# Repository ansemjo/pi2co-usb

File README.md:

# pi2co-usb

This project is based on [i2c-tiny-usb](https://github.com/harbaum/I2C-Tiny-USB/) by Till Harbaum and the [V-USB stack](https://www.obdev.at/products/vusb/index.html) by Objective Development. It uses the fact that you can implement a low-speed USB device with the IO pins on an Atmel AVR chip to create a very simple I2C bridge.

## Hardware

In the original `i2c-tiny-usb` implementation, an Atmel AVR ATtiny45 was used with an external oscillator. Unfortunately this meant, that you needed to use all six pins on the chip, reconfigure the RESET pin and therefore needed a high-voltage serial programmer (HVSP) should anything go wrong.

On more recent Digispark devices, which use an ATtiny85, a modified version of the V-USB stack is used with only the internal PLL oscillator calibrated to 16.5 MHz. No external chrystal is required, ISP remains available and you can even connect an indicator LED on the remaining pin.

I had a couple of Atmel AVR ATtiny85V-10PU chips and a small leftover piece of protoboard. Enough to build myself an I2C bridge! I used a JST-PH connector on the I2C side, which has a slightly too narrow pitch but it works out with a 4-pin connector if you solder it at the edge of the board. Also I had lots of connectors, so I could crimp myself some cables.

Here is a simple [schematic](schematic.pdf) of the protoboard version that you see below on the photos:

## Software

The firmware is almost fully plucked from Till Harbaum's `i2c-tiny-usb` project, so most credit goes to him. I converted the directory to a PlatformIO project, updated the vendored V-USB stack and modified the configuration header to use a different pinout.

It is meant to work together with a current [micronucleus](https://github.com/micronucleus/micronucleus/) bootloader, which allows loading new firmware over the same USB port that is used in the userspace firmware. This implementation also relies on the oscillator calibration included in the bootloader to achieve a stable 16.5 MHz clock.

### Flash the Bootloader

At first I used a default release for the ATtiny85 that I flashed with an ISP programmer and later changed a few options to enable the indicator LED, enter the bootloader only after shorting the RESET pin and disable the timeout. The configuration can be found in `bootloader/t85_pi2co` and can be linked or copied to a micronucleus project under `firmware/configuration/`.

For example, to compile the firmware with the config profile above and flash it with an [Adafruit FT232H breakout](https://wiki.semjonov.de/tips/arduino.html#adafruit-ftdi-ft232h-breakout-board):

```sh
make clean
make CONFIG=t85_pi2co
make CONFIG=t85_pi2co PROGRAMMER="-c ft232h" flash
make CONFIG=t85_pi2co PROGRAMMER="-c ft232h" fuse
```

After that you should be able to speak to the chip with the `micronucleus` commandline application if you connect a USB breakout appropriately. **To enter the bootloader later**, you'll need to reset the chip by briefly shorting the RESET pin to ground.

To allow normal users to speak with the bootloader, apply the
udev rules found in [49-micronucleus.rules](https://github.com/micronucleus/micronucleus/blob/e74ce6f064e0bcbe1c52459a0988187c76834222/commandline/49-micronucleus.rules).

### Flash the Firmware

Now that the bootloader works, install [PlatformIO](https://platformio.org/) and go to the `firmware/` directory. You can now compile the firmware simply by running `pio run`. PlatformIO should handle all framework and platform dependencies for you.

Afterwards flash the firmware by running:

```sh
pio run -t upload
```

**Note:** PlatformIO currently ships an outdated version of the `micronucleus` commandline tool, which won't speak to the current bootloader releases. Either update the binary in `~/.platformio/packages/tool-micronucleus/` or use a current binary with the compiled firmware directly:

```sh
micronucleus .pio/build/tiny85/firmware.hex
```

### Kernel driver

The `i2c-tiny-usb` project has been around for a while, so it already has a driver in the mainline Linux kernel. I only needed to `modprobe i2c-dev` for the device to appear. Install the `i2c-tools` in your Linux distribution of choice and start talking to I2C devices. You may need to run the tools as `root`.

As an example I am reading the date and time from a DS3231 RTC clock:

```sh
$ sudo i2cdetect -l
[sudo] password for ansemjo: 
/* ... */
i2c-10	i2c       	i2c-tiny-usb at bus 001 device 028	I2C adapter
/* ... */

$ sudo i2cdetect -y 10
     0  1  2  3  4  5  6  7  8  9  a  b  c  d  e  f
00:          -- -- -- -- -- -- -- -- -- -- -- -- -- 
10: -- -- -- -- -- -- -- -- -- -- -- -- -- -- -- -- 
20: -- -- -- -- -- -- -- -- -- -- -- -- -- -- -- -- 
30: -- -- -- -- -- -- -- -- -- -- -- -- -- -- -- -- 
40: -- -- -- -- -- -- -- -- -- -- -- -- -- -- -- -- 
50: -- -- -- -- -- -- -- 57 -- -- -- -- -- -- -- -- 
60: -- -- -- -- -- -- -- -- 68 -- -- -- -- -- -- --  << this is the rtc
70: -- -- -- -- -- -- -- --                         

$ i=0; for value in seconds minutes hours weekday day month year; do \
> printf '%7s: %s\n' $value "$(sudo i2cget -y 10 0x68 $i)"; : $((i++)); done
seconds: 0x39
minutes: 0x07
  hours: 0x19
weekday: 0x07
    day: 0x15
  month: 0x03
   year: 0x20
```

The bytes need BCD decoding but you can see the date was `2020-03-15 19:07:39`.

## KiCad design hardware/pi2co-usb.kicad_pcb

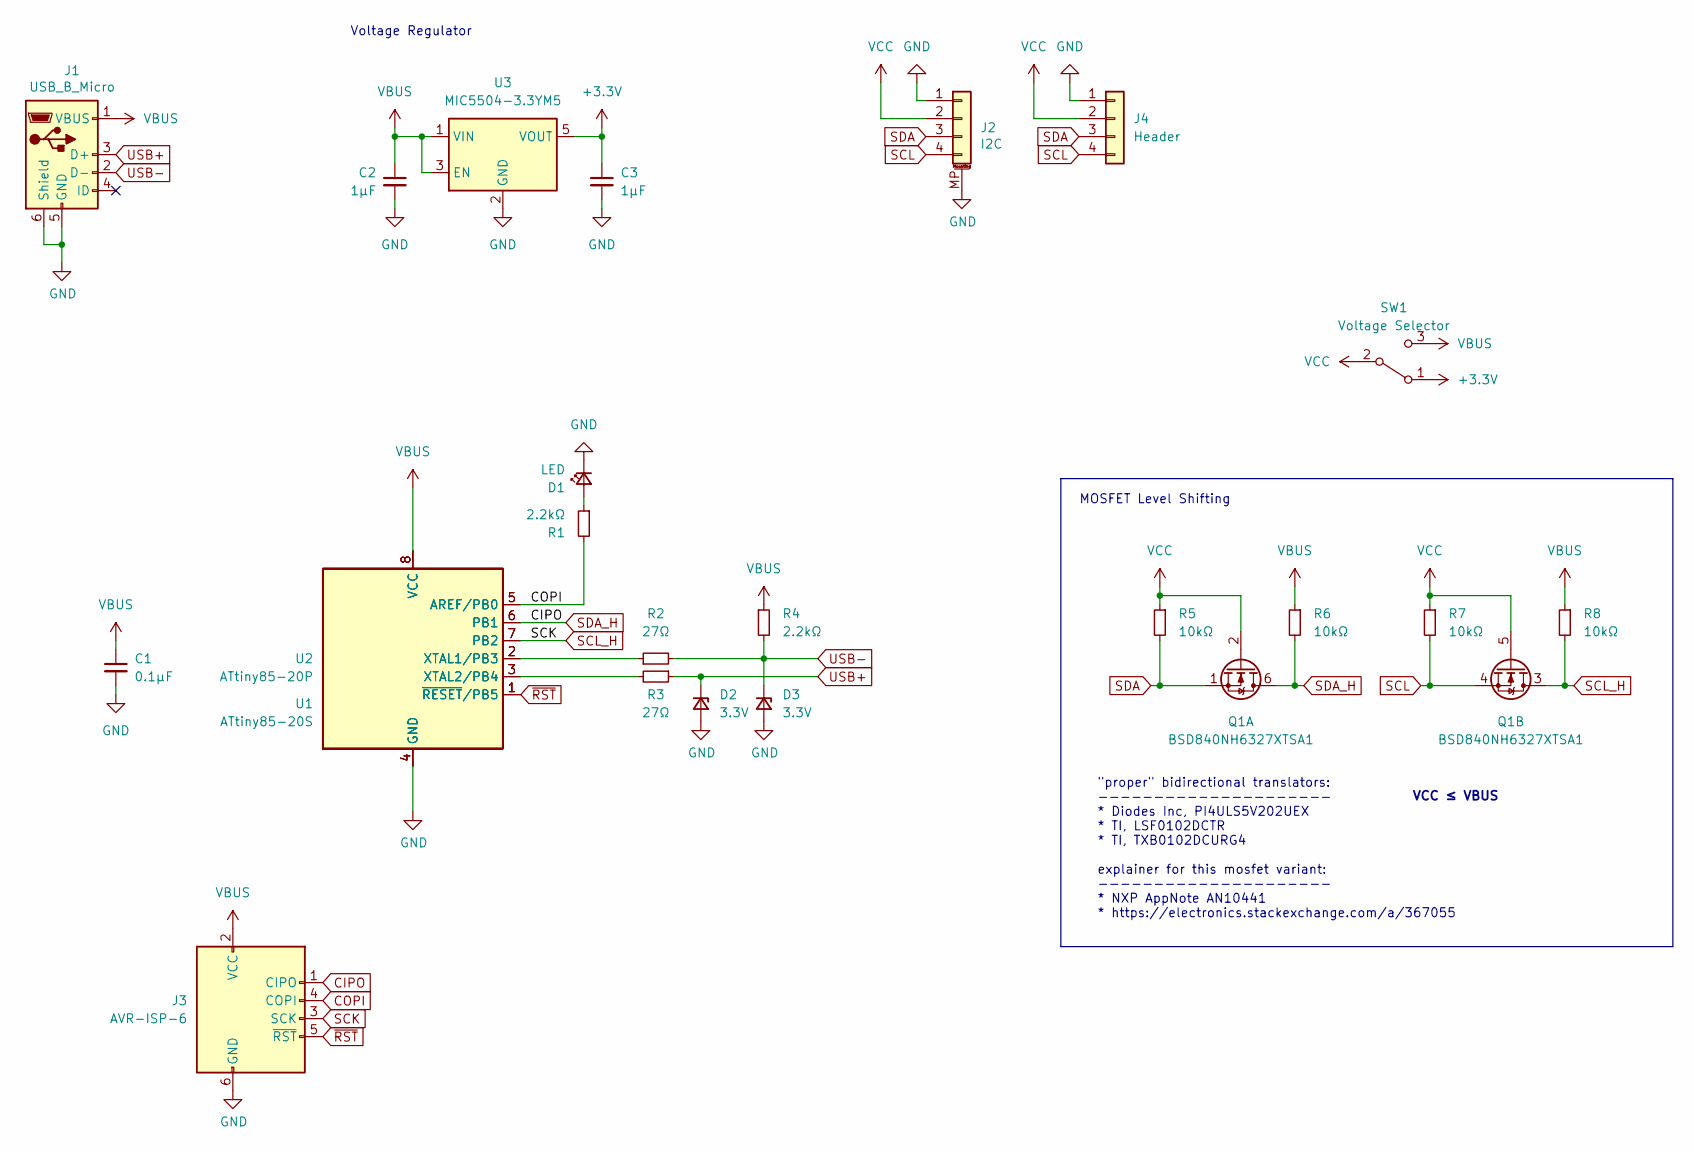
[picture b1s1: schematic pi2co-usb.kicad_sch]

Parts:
C1: 0.1µF; C_0805_2012Metric
C2, C3: 1µF; C_0805_2012Metric
D1: LED; LED_0805_2012Metric
D2, D3: 3.3V; D_SOD-123
J1: USB_B_Micro; USB_Micro-B_Amphenol_10118194_Horizontal
J2: I2C; JST_SH_SM04B-SRSS-TB_1x04-1MP_P1.00mm_Horizontal
J3: AVR-ISP-6; PinHeader_2x03_P2.54mm_Vertical
J4: Header; PinHeader_1x04_P2.54mm_Vertical
Q1: BSD840NH6327XTSA1; SOT-363_SC-70-6
R1, R4: 2.2kΩ; R_0805_2012Metric
R2, R3: 27Ω; R_0805_2012Metric
R5, R6, R7, R8: 10kΩ; R_0805_2012Metric
SW1: Voltage Selector; SW_SPDT_PCM12
U1: ATtiny85-20S; SOIC-8W_5.3x5.3mm_P1.27mm
U2: ATtiny85-20P; DIP-8_W7.62mm
U3: MIC5504-3.3YM5; SOT-23-5

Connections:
+3V3: C3.1, SW1.1 (A), U3.5 (VOUT)
CIPO: J3.1 (CIPO), Q1.6 (D), R6.2, U1.6 (PB1), U2.6 (PB1)
COPI: J3.4 (COPI), R1.2, U1.5 (AREF/PB0), U2.5 (AREF/PB0)
GND: C1.2, C2.2, C3.2, D1.1 (K), D2.2 (A), D3.2 (A), J1.5 (GND), J1.6 (Shield), J2.1, J2.MP (MountPin), J3.6 (GND), J4.1, U1.4 (GND), U2.4 (GND), U3.2 (GND)
unnamed: D1.2 (A), R1.1
unnamed: R2.1, U1.2 (XTAL1/PB3), U2.2 (XTAL1/PB3)
unnamed: R3.2, U1.3 (XTAL2/PB4), U2.3 (XTAL2/PB4)
SCK: J3.3 (SCK), Q1.3 (D), R8.2, U1.7 (PB2), U2.7 (PB2)
SCL: J2.4, J4.4, Q1.4 (S), R7.2
SDA: J2.3, J4.3, Q1.1 (S), R5.2
USB+: D2.1 (K), J1.3 (D+), R3.1
USB-: D3.1 (K), J1.2 (D-), R2.2, R4.2
VBUS: C1.1, C2.1, J1.1 (VBUS), J3.2 (VCC), R4.1, R6.1, R8.1, SW1.3 (C), U1.8 (VCC), U2.8 (VCC), U3.1 (VIN), U3.3 (EN)
VCC: J2.2, J4.2, Q1.2 (G), Q1.5 (G), R5.1, R7.1, SW1.2 (B)
~RST: J3.5 (~RST), U1.1 (~RESET/PB5), U2.1 (~RESET/PB5)

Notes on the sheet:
Voltage Regulator
MOSFET Level Shifting
VCC ≤ VBUS
"proper" bidirectional translators: --------------------- * Diodes Inc, PI4ULS5V202UEX * TI, LSF0102DCTR * TI, TXB0102DCURG4 explainer for this mosfet variant: --------------------- * NXP AppNote AN10441 * https://electronics.stackexchange.com/a/367055

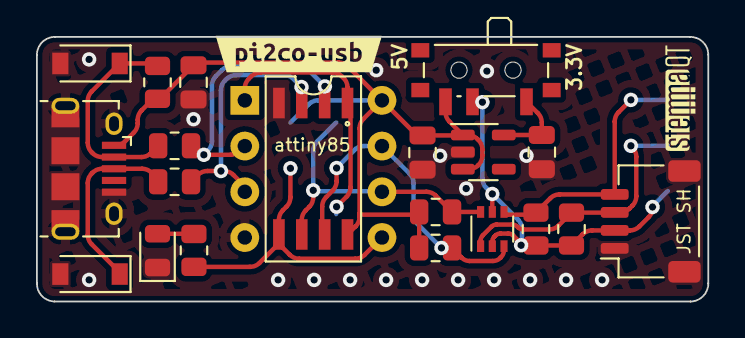
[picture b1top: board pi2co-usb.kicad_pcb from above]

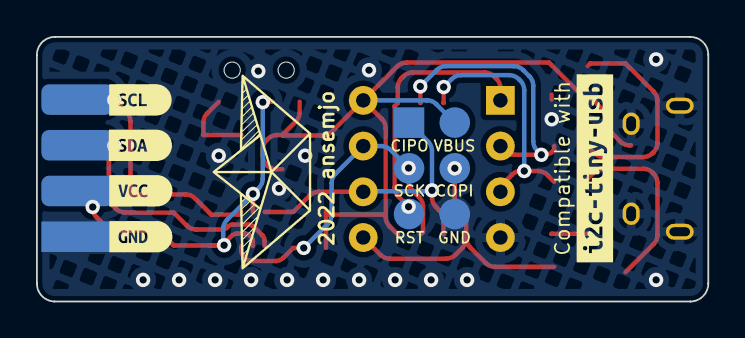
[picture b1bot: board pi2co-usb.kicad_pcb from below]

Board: 2 copper layers, 37.3 x 14.7 mm, 29 parts (7 on the bottom side), 15 nets.

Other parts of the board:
kibuzzard-6233B94D: G***; kibuzzard-6233B94D
kibuzzard-6233B95A: G***; kibuzzard-6233B95A
kibuzzard-6233B920: G***; kibuzzard-6233B920
kibuzzard-6233B938: G***; kibuzzard-6233B938
kibuzzard-6233BAEE: G***; kibuzzard-6233BAEE
kibuzzard-6233C230: G***; kibuzzard-6233C230

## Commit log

2020-03-15 begin tracking functioning firmware directory
2020-03-15 add readme and full project structure
2020-03-15 fix typo
2020-03-15 fix another typo
2020-03-15 add schematic as kicad .sch and plotted pdf/svg
2020-03-15 add release directory with compiled firmware and standalone instructions
2022-03-17 kicad project for proper pcb incl. level shifting
2022-03-18 add makefile with kikit panelization and fab
2022-03-18 add panelized data for jlc
2022-04-02 add ibom.html for assembly
2022-04-02 update readme and move old schematic to prototype/
